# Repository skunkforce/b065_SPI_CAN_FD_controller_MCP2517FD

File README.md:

# edgy_board number b065
This design is part of the [edgy board project](https://github.com/skunkforce/edgy_boards).

# getting started
This repository uses submodules. After cloning use the command 

```$ git submodule update --init --recursive```

to pull the submodules before opening the project with kicad. 

# Tests
Tests can be found in [TESTS.md](TESTS.md)

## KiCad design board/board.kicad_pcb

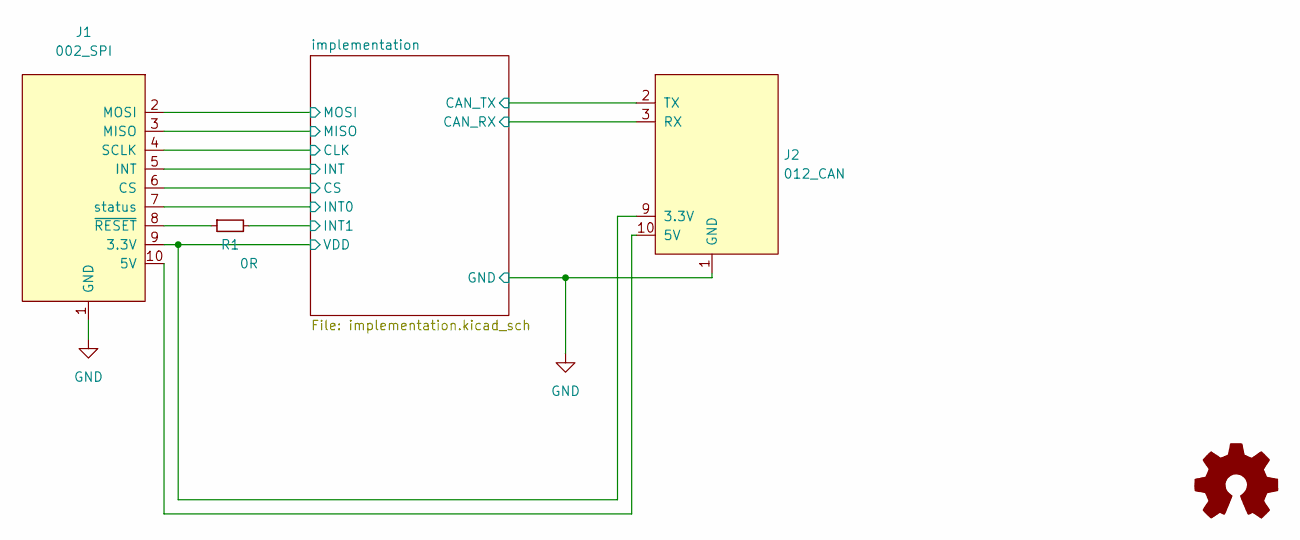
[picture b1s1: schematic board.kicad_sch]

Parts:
J1: 002_SPI; on_edge_2x05_device
J2: 012_CAN; on_edge_2x05_host
LOGO1: Logo_Open_Hardware_Small; OSHW-Symbol_6.7x6mm_SilkScreen
R1: 0R; R_0603_1608Metric

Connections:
/implementation/CAN_RX: J2.3 (RX); also elsewhere on the board
/implementation/CAN_TX: J2.2 (TX); also elsewhere on the board
/implementation/CLK: J1.4 (SCLK); also elsewhere on the board
/implementation/CS: J1.6 (CS); also elsewhere on the board
/implementation/INT: J1.5 (INT); also elsewhere on the board
/implementation/INT0: J1.7 (status); also elsewhere on the board
/implementation/INT1: R1.2; also elsewhere on the board
/implementation/MISO: J1.3 (MISO); also elsewhere on the board
/implementation/MOSI: J1.2 (MOSI); also elsewhere on the board
/implementation/VDD: J1.9 (3.3V), J2.9 (3.3V); also elsewhere on the board
GND: J1.1 (GND), J2.1 (GND); also elsewhere on the board
unnamed: J1.8 (~RESET), R1.1
unnamed: J1.10 (5V), J2.10 (5V)

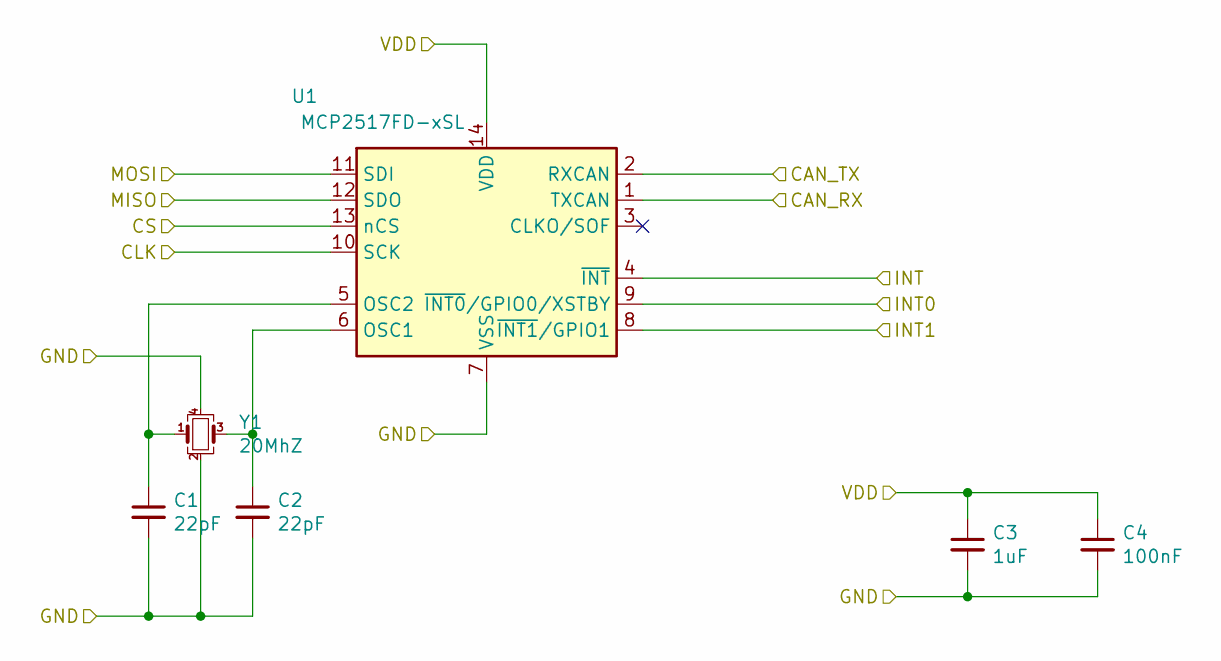
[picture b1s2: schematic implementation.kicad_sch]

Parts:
C1, C2: 22pF; C_0603_1608Metric; Voltage 6.3V
C3: 1uF; C_0603_1608Metric; Voltage 6.3V
C4: 100nF; C_0603_1608Metric; Voltage 6.3V
U1: MCP2517FD-xSL; SOIC-14_3.9x8.7mm_P1.27mm; MPN MCP2517FD-H/SL; Digi-Key_PN MCP2517FDT-H/SLCT-ND
Y1: 20MhZ; Crystal_SMD_Abracon_ABM8G-4Pin_3.2x2.5mm; MPN ECS-200-18-33-JGN-TR

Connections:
/implementation/CAN_RX: U1.1 (TXCAN); also elsewhere on the board
/implementation/CAN_TX: U1.2 (RXCAN); also elsewhere on the board
/implementation/CLK: U1.10 (SCK); also elsewhere on the board
/implementation/CS: U1.13 (nCS); also elsewhere on the board
/implementation/INT: U1.4 (~INT); also elsewhere on the board
/implementation/INT0: U1.9 (~INT0/GPIO0/XSTBY); also elsewhere on the board
/implementation/INT1: U1.8 (~INT1/GPIO1); also elsewhere on the board
/implementation/MISO: U1.12 (SDO); also elsewhere on the board
/implementation/MOSI: U1.11 (SDI); also elsewhere on the board
/implementation/VDD: C3.1, C4.1, U1.14 (VDD); also elsewhere on the board
GND: C1.2, C2.2, C3.2, C4.2, U1.7 (VSS), Y1.2, Y1.4; also elsewhere on the board
unnamed: C1.1, U1.5 (OSC2), Y1.1
unnamed: C2.1, U1.6 (OSC1), Y1.3

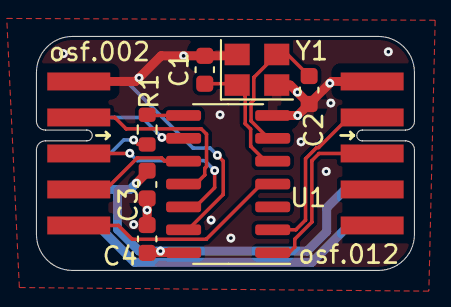
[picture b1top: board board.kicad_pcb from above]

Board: 2 copper layers, 21.0 x 13.0 mm, 10 parts (1 on the bottom side), 15 nets.

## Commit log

2023-05-02 initial
2023-05-03 added render
2023-05-27 renamed subsheet to work better in compositions
